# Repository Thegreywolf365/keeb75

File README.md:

# Keeb75
 PCB bring up for a 75 key, completely programmable, customisable USB-C compliant keyboard, with compatibility for cherry mx style switches.

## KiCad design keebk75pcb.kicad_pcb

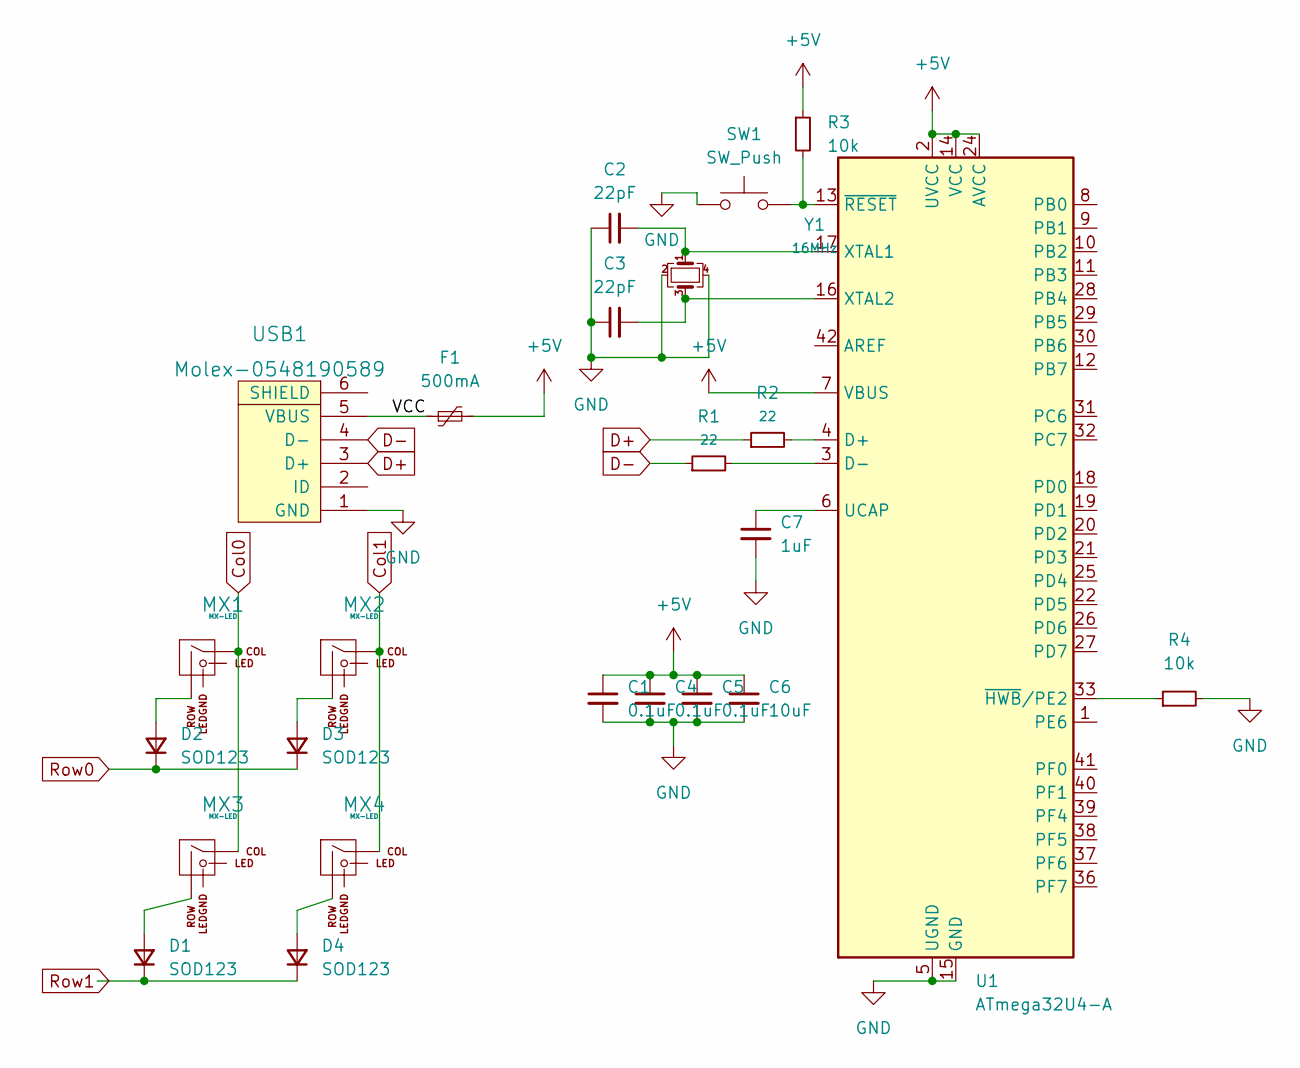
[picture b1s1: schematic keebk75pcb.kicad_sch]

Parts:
C1, C4, C5: 0.1uF; C_0805_2012Metric
C2, C3: 22pF; C_0805_2012Metric
C6: 10uF; C_0805_2012Metric
C7: 1uF; C_0805_2012Metric
D1, D2, D3, D4: SOD123; D_SOD-123
F1: 500mA; Fuse_1206_3216Metric
MX1, MX2, MX3, MX4: MX-LED; MXOnly-1U-Hotswap-LED
R1, R2: 22; R_0805_2012Metric
R3, R4: 10k; R_0805_2012Metric
SW1: SW_Push; SKQG-1155865
U1: ATmega32U4-A; TQFP-44_10x10mm_P0.8mm
USB1: Molex-0548190589
Y1: 16MHz; Crystal_SMD_3225-4Pin_3.2x2.5mm_HandSoldering

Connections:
+5V: C1.1, C4.1, C5.1, C6.1, F1.2, R3.1, U1.2 (UVCC), U1.7 (VBUS), U1.14 (VCC), U1.24 (AVCC), U1.34 (VCC), U1.44 (AVCC)
/VCC: F1.1, USB1.5 (VBUS)
Col0: MX1.1 (COL), MX3.1 (COL), U1.29 (PB5)
Col1: MX2.1 (COL), MX4.1 (COL), U1.28 (PB4)
D+: R2.1, USB1.3 (D+)
D-: R1.1, USB1.4 (D-)
GND: C1.2, C2.1, C3.1, C4.2, C5.2, C6.2, C7.2, R4.2, SW1.1, U1.5 (UGND), U1.15 (GND), U1.23 (GND), U1.35 (GND), U1.43 (GND), USB1.1 (GND), Y1.2, Y1.4
unnamed: C2.2, U1.17 (XTAL1), Y1.1
unnamed: C3.2, U1.16 (XTAL2), Y1.3
unnamed: C7.1, U1.6 (UCAP)
unnamed: D1.2 (A), MX3.2 (ROW)
unnamed: D2.2 (A), MX1.2 (ROW)
unnamed: D3.2 (A), MX2.2 (ROW)
unnamed: D4.2 (A), MX4.2 (ROW)
unnamed: R1.2, U1.3 (D-)
unnamed: R2.2, U1.4 (D+)
unnamed: R3.2, SW1.2, U1.13 (~RESET)
unnamed: R4.1, U1.33 (~HWB/PE2)
Row0: D2.1 (K), D3.1 (K), U1.27 (PD7)
Row1: D1.1 (K), D4.1 (K), U1.30 (PB6)

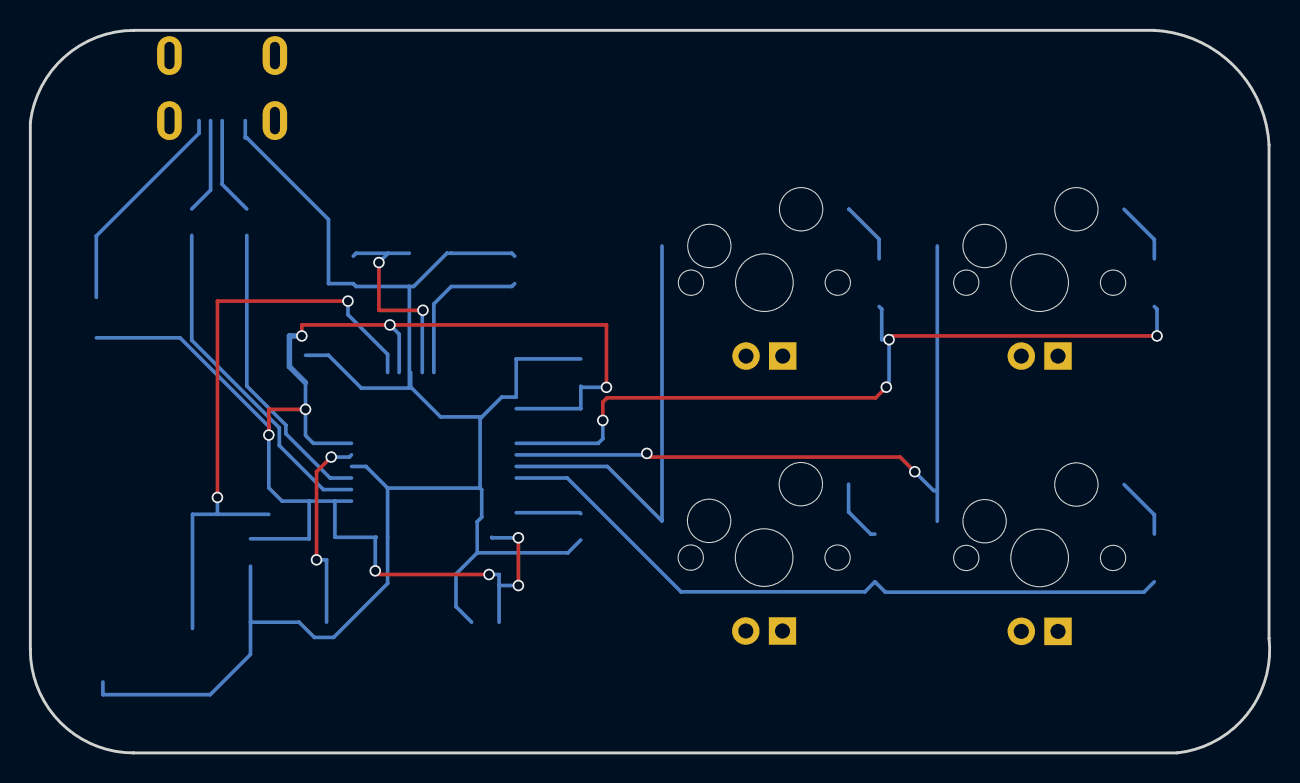
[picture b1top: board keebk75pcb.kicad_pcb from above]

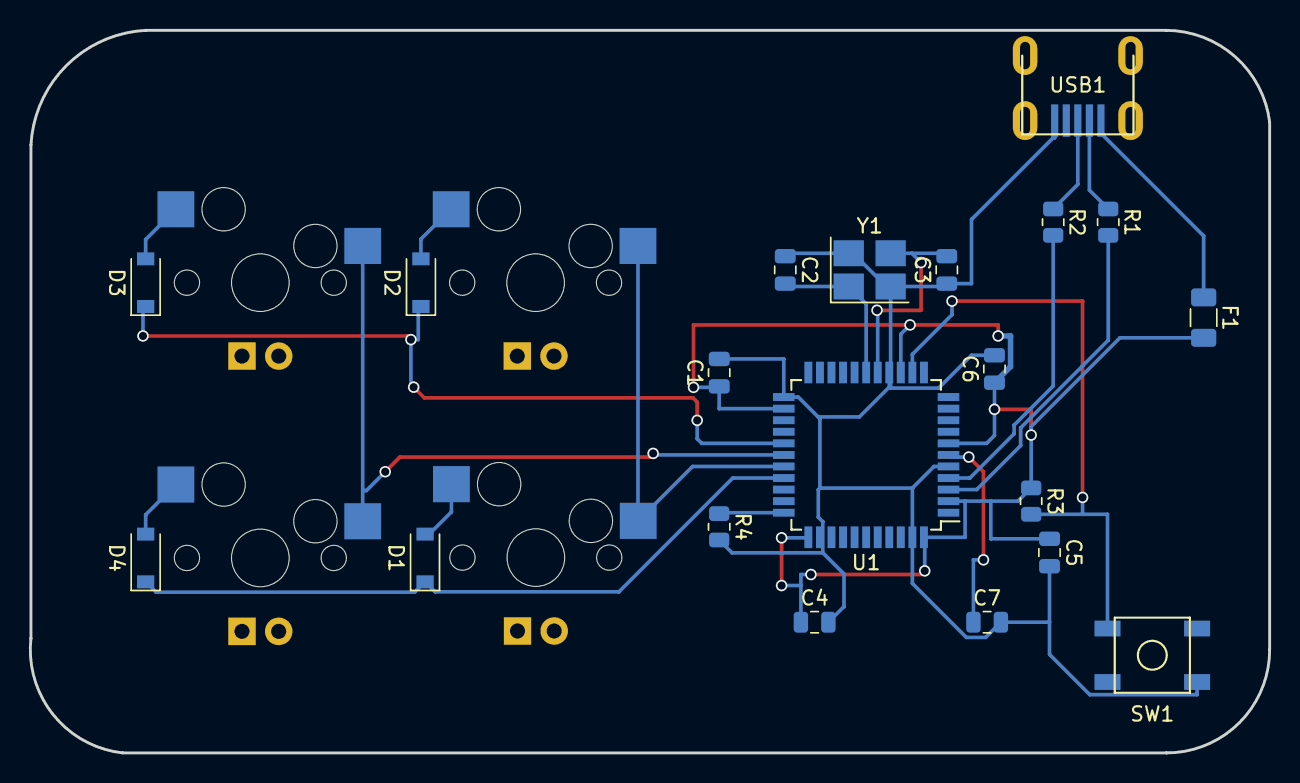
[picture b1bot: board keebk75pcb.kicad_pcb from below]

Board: 2 copper layers, 85.8 x 50.0 mm, 24 parts (20 on the bottom side), 20 nets.

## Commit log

2022-02-05 init kicad
2022-02-05 submodules
2022-02-05 cherry breakout-1
2022-02-05 proj-spef-lib footprint lib
2022-02-05 auto
2022-02-06 finpcbsch
2022-02-06 layout
2022-02-06 routing
